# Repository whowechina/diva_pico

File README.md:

# Diva Pico - Project Diva Style Mini Controller
[点这里可以切换到中文版](README_CN.md)

Features:
* Two sizes, Diva Pico and Diva Pico+.
* It's small, but the buttons are still decent.
* Support Nintendo Switch, Steam PC and Arcade version.
* HID light for Arcade version.
* All source files open.

Thanks to many respectful guys/companies who made their tools or materials free or open source (KiCad, OnShape, InkScape, Raspberry things).

Special thanks to community developers that inspired me and helped me: CrazyRedMachine (https://github.com/CrazyRedMachine).

And also:
* GP2040-CE: https://gp2040-ce.info/ (for the PS4 support)
* RP_Silicon_KiCad: https://github.com/HeadBoffin/RP_Silicon_KiCad
* Switch_Keyboard_Kailh: https://github.com/kiswitch/keyswitch-kicad-library

## Notes
This Diva Pico project:  
* Heavily depends on 3D printing, you need a Bambu 3D printer (X1, P1 or A1, not the mini version).
* Requires skills to solder tiny components.

## My Other Projects
You can check out my other cool projects.

* Popn Pico: https://github.com/whowechina/popn_pico
* IIDX Pico: https://github.com/whowechina/iidx_pico
* Chu Pico: https://github.com/whowechina/chu_pico
* Mai Pico: https://github.com/whowechina/mai_pico
* Diva Pico: https://github.com/whowechina/diva_pico
* AIC Pico: https://github.com/whowechina/aic_pico
* Groove Pico: https://github.com/whowechina/groove_pico
* Geki Pico: https://github.com/whowechina/geki_pico
* Musec Pico: https://github.com/whowechina/musec_pico
* Ju Pico: https://github.com/whowechina/ju_pico
* Bishi Pico: https://github.com/whowechina/bishi_pico
* Nos Pico: https://github.com/whowechina/nos_pico
* Voltex Pico: https://github.com/whowechina/voltex_pico
* Chord Pico: https://github.com/whowechina/chord_pico
* Dance Pico: https://github.com/whowechina/dance_pico
* Arcade Pico: https://github.com/whowechina/arcade_pico

## **Disclaimer** ##
I made this project in my personal time with no financial benefit or sponsorship. I will continue to improve the project. I have done my best to ensure that everything is accurate and functional, there's always a chance that mistakes may occur. I cannot be held responsible for any loss of your time or money that may result from using this open source project. Thank you for your understanding.

## About the License
It's CC-NC. So DIY for yourself and for your friend, don't make money from it. And plagiarism that doesn’t even dare to mention the original author is not acceptable. Plase note that pooling orders and group buying for raw materials is acceptable. Selling off any leftover components without profit is also acceptable.

If you're interested in some kind of commercial use, please contact me (Discord, QQ group, Wechat group or leave your contact in issue section).

## My Discord Invitation
https://discord.gg/M8f2PPQFEA

## HOW TO BUILD
### Frequently Made Mistakes
Many DIY enthusiasts commonly make certain mistakes during the building process. Please proceed with extra caution to avoid these.
* **MISTAKE: Soldering everything together without conducting intermediate testing.**  
  Remember, even professional engineers can make mistakes. It becomes significantly harder to identify the root cause of a problem when all components are already assembled or soldered. Therefore, it's advisable to solder and test in stages. The firmware is designed to function correctly even with some components missing, which is good for testing.
* **MISTAKE: Neglecting to cut the ADDR pin trace on the MPR121 module.**  
  The MPR121 module in the market has the ADDR pin pre-connected to ground. But the board expects a floating ADDR pin, otherwise the ADDR pin will short the circuit. Please verify your "CUT" using a multimeter.
* **MISTAKE: Rushing to replace components when something fails.**  
  Sometimes people prematurely assumes that the Raspberry Pi Pico or other modules are faulty.
  Be aware that desoldering and soldering large SMD components is a challenging task. It carries the risk of damaging the component or the PCB board. Patience and caution are crucial. Look at the schematics and PCB design files and ask help from community first. Questioning the integrity of these components should be your last resort.

### PCB
* Choose a PCB vendor (such as JLCPCB) and place an order with the gerber zip file (latest `Production\PCB\diva_xxx_xxx.zip`), regular FR-4 board, black color, thickness is **1.6mm**.  

* 1x Rasberry Pico Pi Pico or **pin-to-pin** compatible clones.  
  https://www.raspberrypi.com/products/raspberry-pi-pico  
  Sticking a thin scotch tape to avoid short-circuit is a good idea.  

* 16x WS2812B-4020 (32x for Diva Pico+) side-facing RGB LEDs for the slider.  
  https://www.lcsc.com/product-detail/Light-Emitting-Diodes-LED_Worldsemi-WS2812B-4020_C965557.html
* 9x WS2812B-3528 RGB LEDs for Diva Pico buttons. For Diva Pico+, you need 17x WS2812B-3528 reverse mount RGB LEDs.

* 2x MPR121 modules (3x for Diva Pico+), there're many types in the market, choose ones like this.  
  https://www.sparkfun.com/products/retired/9695  
  Before solder MP121 module to the main PCB board, remember to use a knife to **cut (unshort) the tiny trace that connects ADDR to the GND**. You can cut the red part as shown in the image. Please be careful not to cut more than necessary.  

* 8x 0603 1uF (0.1~1uF all fine) capacitors (C1 to C8), OPTIONAL, recommended.

* 4x Kailh choc v1 switches, dark yellow is recommeded for its 70gf force.  

* 2x Alps SKSTAAE010 tactile switches.
  https://tech.alpsalpine.com/e/products/detail/SKSTAAE010/

* 1x Omron B3F-4005 or B3F-4000 micro-switch.
  https://www.mouser.com/ProductDetail/Omron-Electronics/B3F-4000?qs=B3tblJ0Nlt8c5sbFRctxww%3D%3D

* For Diva Pico only, 3M 5423 or 5421 UHMW PE film tape, important for button feel. 5423 is better for its thickness.  
  https://www.3m.com/3M/en_US/p/d/b40069119/

  You need to apply tapes to the contact surface of button to switch and button to base clamp.  

* For Diva Pico only, 4x 2mm\*50mm (diameter\*length) steel rods for the button lever structure.

* For Diva Pico+ only, 8x U-shape 2U stabilizer steel wires, you can also harvest them from regular 2U MX stabilizers. I invented this structure originally in my Voltex Pico project, checkout Voltex Pico repository for more details.

* For Diva Pico+ only, 4x 3mm\*5mm\*10mm regular springs for increasing the button force.

### Light Guide Panel
* Find a service to cut a light guide panel or a frosted acrylic panel. It's a perfect rectangle, 1.8mm to 2.0mm thickness
  * For Diva Pico, the size is 240mm\*42mm.
  * For Diva Pico+, the size is 329mm\*47mm.
* This is what a decent light guide panel looks like.  

### 3D Printing
* You might need a Bambu 3D printer:
  *  For Diva Pico, a 256\*256mm bed is fine; for Diva Pico+ you need a H2D-sized bed.
  * Its AMS system works great for multi-color printing.
* Printing parameters  
  * PLA, PETG, ABS are all OK.
  * The color "Arctic Whisper" works best for the main body.
  * Layer height: 0.2mm
  * Support: Yes, always.

* Base: `Production\3D\diva_xxx_base.stl`.
* Cover Base: `Production\3D\diva_xxx_support.stl`.
* Cover: `Production\3D\diva_xxx_panel.3mf`, with multi-color support.
* Buttons: `Production\3D\diva_xxx_button_combo.3mf`, with multi-color support.  
  Note that button components (the button body, the seat and the logos on it) are mixed in one file, you need to cherry-pick before printing.  

From top to bottom:
* Cover
* Cover Base + Light Guide Panel
* Buttons
* PCB
* Base

For Diva Pico, you need **6x M3*10mm regular screws** to fix all things. For Diva Pico+, you need **9x M3\*8mm** regular screws and **4x M2\*8mm** flat head screws.

Apply some 10mm\*2mm silicone anti-slip pads to the bottom side of the base to provide stability when playing.  

#### Button dome choices
* Go buy 60mm dome buttons.
  * For Diva Pico+, a regular 60mm arcade dome button is fine.
  * For Diva Pico, you should get this specific one, its inner diameter is 46mm.  

### Firmware
* UF2 file is in `Production\Firmware` folder.
* For the new build, hold the BOOTSEL button while connect the USB to a PC, there will be a disk named "RPI-RP2" showed up. Drag the UF2 firmware binary file into it. That's it. There's a small hole at the bottom side of the Diva Pico, it is facing right to the BOOTSEL button.
* It has a command line to do configuration. You can use this Web Serial Terminal to connect to the USB serial port of the Diva Pico. (Note: "?" is for help)  
  https://googlechromelabs.github.io/serial-terminal/  
* You can switch key mapping mode using either of the following methods:
  * Hold Triangle, Square, Cross, Circle or Cross+Circle while plugging in the USB cable to switch to Nintendo Switch, PC Steam, Arcade, PlayStation and PlayStation Arcade mode, respectively.
  * Use the `keymap` command in the command line interface.
* In Nintendo Switch, PC Steam, and PlayStation modes, the left auxiliary button is used as a "SHIFT" key, changing the functions of the other six buttons.
* In PlayStation mode, if key-related files are missing, the console will disconnect controller input after 8 minutes. You can use the following tool to set a PS key.  
  https://whowechina.github.io/diva_pico/tools/ps4key_packer.html
  * **Note** The Diva Pico project will not provide any files or information related to acquiring these files. Do not request them through any communication channel (e.g., Email, Instant Messaging, GitHub Issues, Discord).

## CAD Source File
I'm using OnShape free subscription. It's powerful but it can't archive original designs to local, so I can only share the link here. STL/DXF/DWG files are exported from this online document.  
https://cad.onshape.com/documents/d9e9c1de2d4b98d5eaf21d07/w/7c216f367b558e083eb1f468/e/4536bf9859137db81313ff87?configuration=List_ilV09d08Sdz7FZ%3DButton_48&renderMode=0&uiState=65923e1383b3106c15b5c996

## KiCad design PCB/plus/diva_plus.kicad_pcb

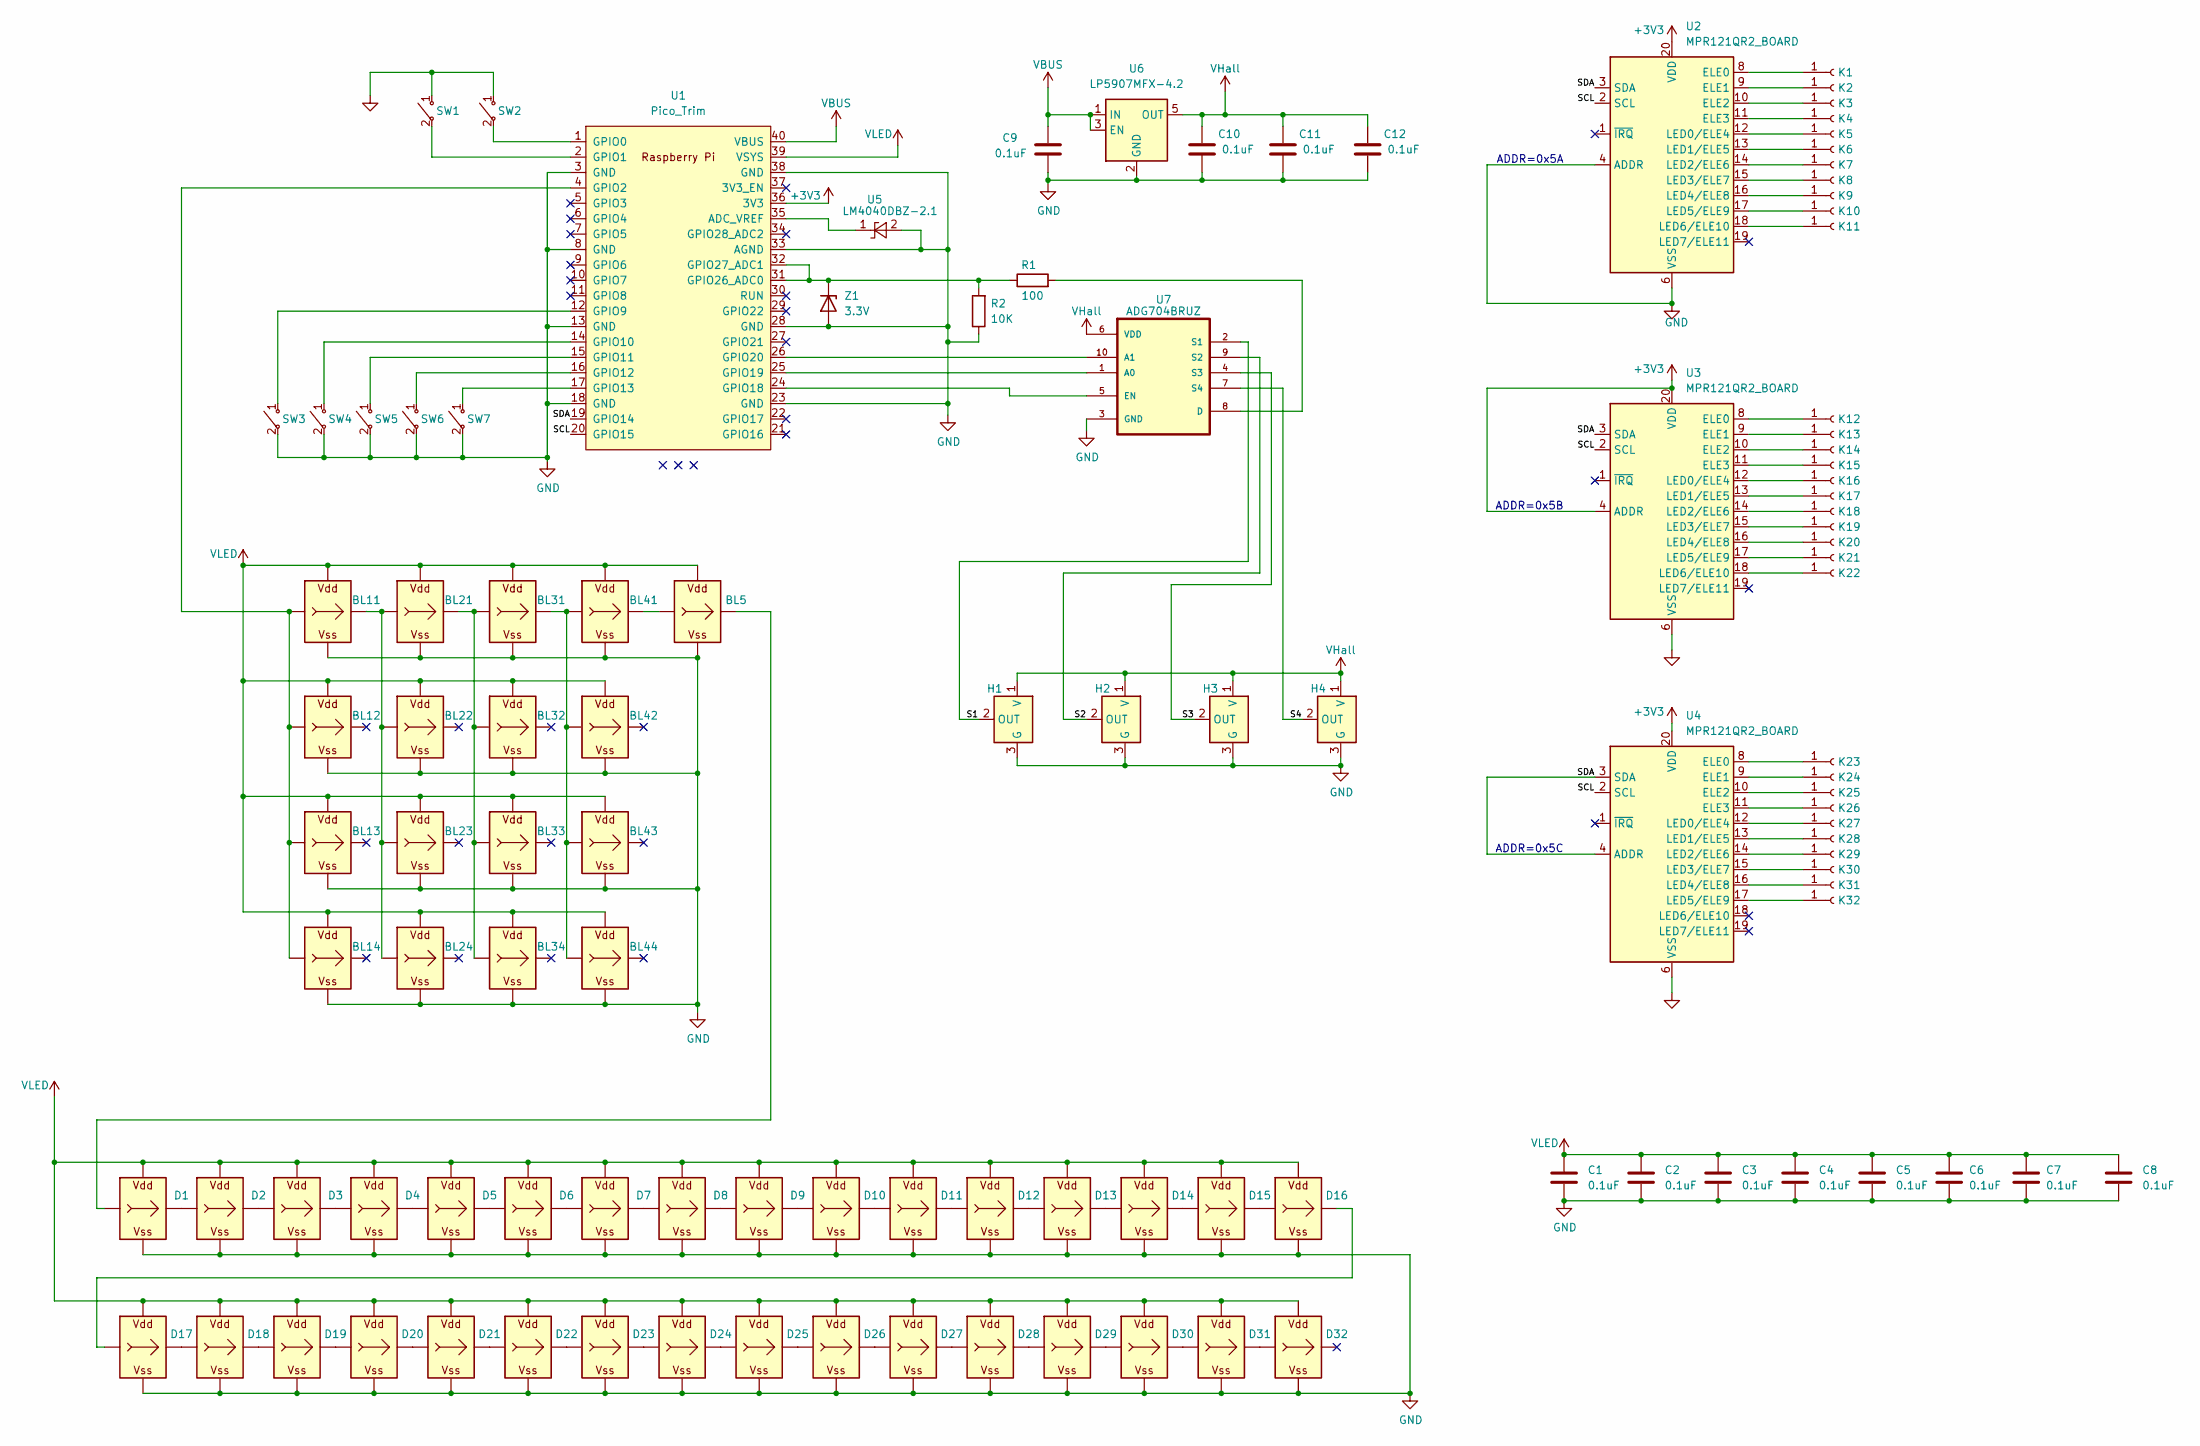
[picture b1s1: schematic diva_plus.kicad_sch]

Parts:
BL5, BL11, BL12, BL13, BL14, BL21, BL22, BL23, BL24, BL31, BL32, BL33, BL34, BL41, BL42, BL43, BL44: WS2812B_Unified; WS2812B-2835_EMBED
C1, C2, C3, C4, C5, C6, C7, C8, C9, C10, C11, C12: 0.1uF; C_0603_1608Metric_Pad1.08x0.95mm_HandSolder
D1, D2, D3, D4, D5, D6, D7, D8, D9, D10, D11, D12, D13, D14, D15, D16, D17, D18, D19, D20, D21, D22, D23, D24, D25, D26, D27, D28, D29, D30, D31, D32: WS2812B_Unified; WS2812B-4020
H1, H2, H3, H4: SS49E_SOT23; SOT-23-FAT
K1, K2, K3, K4, K5, K6, K7, K8, K9, K10, K13, K14, K15, K16, K18, K19, K20, K21, K24, K25, K26, K27, K28, K29, K30, K31, K32: Conn_01x01_Female; DivaKey
K11, K22: Conn_01x01_Female; DivaKeyBiasLeft
K12, K17, K23: Conn_01x01_Female; DivaKeyBiasRight
R1: 100; R_0603_1608Metric_Pad0.98x0.95mm_HandSolder
R2: 10K; R_0603_1608Metric_Pad0.98x0.95mm_HandSolder
SW1, SW2: SWITCH_SPST; SKSTAAE010
SW3, SW4, SW5, SW6: SWITCH_SPST; Choc_HE
SW7: SWITCH_SPST; B3F4000
U1: Pico_Trim; RPi_Pico_SMD_No_USB
U2, U3, U4: MPR121QR2_BOARD; MPR121_BOARD
U5: LM4040DBZ-2.1; SOT-23-FAT
U6: LP5907MFX-4.2; SOT-23-5
U7: ADG704BRUZ; TSSOP-10_3x3mm_P0.5mm
Z1: 3.3V; D_SOD-123F

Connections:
+3V3: U1.36 (3V3), U2.20 (VDD), U3.4 (ADDR), U3.20 (VDD), U4.20 (VDD)
/S1: H1.2 (OUT), U7.2 (S1)
/S2: H2.2 (OUT), U7.9 (S2)
/S3: H3.2 (OUT), U7.4 (S3)
/S4: H4.2 (OUT), U7.7 (S4)
/SCL: U1.20 (GPIO15), U2.2 (SCL), U3.2 (SCL), U4.2 (SCL)
/SDA: U1.19 (GPIO14), U2.3 (SDA), U3.3 (SDA), U4.3 (SDA), U4.4 (ADDR)
GND: BL5.G (VSS), BL11.G (VSS), BL12.G (VSS), BL13.G (VSS), BL14.G (VSS), BL21.G (VSS), BL22.G (VSS), BL23.G (VSS), BL24.G (VSS), BL31.G (VSS), BL32.G (VSS), BL33.G (VSS), BL34.G (VSS), BL41.G (VSS), BL42.G (VSS), BL43.G (VSS), BL44.G (VSS), C1.2, C2.2, C3.2, C4.2, C5.2, C6.2, C7.2, C8.2, C9.2, C10.2, C11.2, C12.2, D1.G (VSS), D2.G (VSS), D3.G (VSS), D4.G (VSS), D5.G (VSS), D6.G (VSS), D7.G (VSS), D8.G (VSS), D9.G (VSS), D10.G (VSS), D11.G (VSS), D12.G (VSS), D13.G (VSS), D14.G (VSS), D15.G (VSS), D16.G (VSS), D17.G (VSS), D18.G (VSS), D19.G (VSS), D20.G (VSS), D21.G (VSS), D22.G (VSS), D23.G (VSS), D24.G (VSS), D25.G (VSS), D26.G (VSS), D27.G (VSS), D28.G (VSS), D29.G (VSS), D30.G (VSS), D31.G (VSS), D32.G (VSS), H1.3 (G), H2.3 (G), H3.3 (G), H4.3 (G), R2.1, SW1.1 ("~"), SW2.1 ("~"), SW3.2 ("~"), SW4.2 ("~"), SW5.2 ("~"), SW6.2 ("~"), SW7.2 ("~"), U1.3 (GND), U1.8 (GND), U1.13 (GND), U1.18 (GND), U1.23 (GND), U1.28 (GND), U1.33 (AGND), U1.38 (GND), U2.4 (ADDR), U2.6 (VSS), U3.6 (VSS), U4.6 (VSS), U5.2 (A), U6.2 (GND), U7.3 (GND), Z1.2 (A)
unnamed: BL5.O (Out), D1.I (In)
unnamed: BL11.I (In), BL12.I (In), BL13.I (In), BL14.I (In), U1.4 (GPIO2)
unnamed: BL11.O (Out), BL21.I (In), BL22.I (In), BL23.I (In), BL24.I (In)
unnamed: BL21.O (Out), BL31.I (In), BL32.I (In), BL33.I (In), BL34.I (In)
unnamed: BL31.O (Out), BL41.I (In), BL42.I (In), BL43.I (In), BL44.I (In)
unnamed: BL5.I (In), BL41.O (Out)
unnamed: D1.O (Out), D2.I (In)
unnamed: D2.O (Out), D3.I (In)
unnamed: D3.O (Out), D4.I (In)
unnamed: D4.O (Out), D5.I (In)
unnamed: D5.O (Out), D6.I (In)
unnamed: D6.O (Out), D7.I (In)
unnamed: D7.O (Out), D8.I (In)
unnamed: D8.O (Out), D9.I (In)
unnamed: D9.O (Out), D10.I (In)
unnamed: D10.O (Out), D11.I (In)
unnamed: D11.O (Out), D12.I (In)
unnamed: D12.O (Out), D13.I (In)
unnamed: D13.O (Out), D14.I (In)
unnamed: D14.O (Out), D15.I (In)
unnamed: D15.O (Out), D16.I (In)
unnamed: D16.O (Out), D17.I (In)
unnamed: D17.O (Out), D18.I (In)
unnamed: D18.O (Out), D19.I (In)
unnamed: D19.O (Out), D20.I (In)
unnamed: D20.O (Out), D21.I (In)
unnamed: D21.O (Out), D22.I (In)
unnamed: D22.O (Out), D23.I (In)
unnamed: D23.O (Out), D24.I (In)
unnamed: D24.O (Out), D25.I (In)
unnamed: D25.O (Out), D26.I (In)
unnamed: D26.O (Out), D27.I (In)
unnamed: D27.O (Out), D28.I (In)
unnamed: D28.O (Out), D29.I (In)
unnamed: D29.O (Out), D30.I (In)
unnamed: D30.O (Out), D31.I (In)
unnamed: D31.O (Out), D32.I (In)
unnamed: K1.1, U2.8 (ELE0)
unnamed: K2.1, U2.9 (ELE1)
unnamed: K3.1, U2.10 (ELE2)
unnamed: K4.1, U2.11 (ELE3)
unnamed: K5.1, U2.12 (LED0/ELE4)
unnamed: K6.1, U2.13 (LED1/ELE5)
unnamed: K7.1, U2.14 (LED2/ELE6)
unnamed: K8.1, U2.15 (LED3/ELE7)
unnamed: K9.1, U2.16 (LED4/ELE8)
unnamed: K10.1, U2.17 (LED5/ELE9)
unnamed: K11.1, U2.18 (LED6/ELE10)
unnamed: K12.1, U3.8 (ELE0)
unnamed: K13.1, U3.9 (ELE1)
unnamed: K14.1, U3.10 (ELE2)
unnamed: K15.1, U3.11 (ELE3)
unnamed: K16.1, U3.12 (LED0/ELE4)
unnamed: K17.1, U3.13 (LED1/ELE5)
unnamed: K18.1, U3.14 (LED2/ELE6)
unnamed: K19.1, U3.15 (LED3/ELE7)
unnamed: K20.1, U3.16 (LED4/ELE8)
unnamed: K21.1, U3.17 (LED5/ELE9)
unnamed: K22.1, U3.18 (LED6/ELE10)
unnamed: K23.1, U4.8 (ELE0)
unnamed: K24.1, U4.9 (ELE1)
unnamed: K25.1, U4.10 (ELE2)
unnamed: K26.1, U4.11 (ELE3)
unnamed: K27.1, U4.12 (LED0/ELE4)
unnamed: K28.1, U4.13 (LED1/ELE5)
unnamed: K29.1, U4.14 (LED2/ELE6)
unnamed: K30.1, U4.15 (LED3/ELE7)
unnamed: K31.1, U4.16 (LED4/ELE8)
unnamed: K32.1, U4.17 (LED5/ELE9)
unnamed: U1.35 (ADC_VREF), U5.1 (K)
unnamed: SW2.2 ("~"), U1.1 (GPIO0)
unnamed: SW1.2 ("~"), U1.2 (GPIO1)
unnamed: SW3.1 ("~"), U1.12 (GPIO9)
unnamed: SW4.1 ("~"), U1.14 (GPIO10)
unnamed: SW5.1 ("~"), U1.15 (GPIO11)
unnamed: SW6.1 ("~"), U1.16 (GPIO12)
unnamed: SW7.1 ("~"), U1.17 (GPIO13)
unnamed: U1.24 (GPIO18), U7.5 (EN)
unnamed: U1.25 (GPIO19), U7.1 (A0)
unnamed: U1.26 (GPIO20), U7.10 (A1)
unnamed: R1.1, R2.2, U1.31 (GPIO26_ADC0), U1.32 (GPIO27_ADC1), Z1.1 (K)
unnamed: R1.2, U7.8 (D)
VBUS: C9.1, U1.40 (VBUS), U6.1 (IN), U6.3 (EN)
VHall: C10.1, C11.1, C12.1, H1.1 (V), H2.1 (V), H3.1 (V), H4.1 (V), U6.5 (OUT), U7.6 (VDD)
VLED: BL5.V (VDD), BL11.V (VDD), BL12.V (VDD), BL13.V (VDD), BL14.V (VDD), BL21.V (VDD), BL22.V (VDD), BL23.V (VDD), BL24.V (VDD), BL31.V (VDD), BL32.V (VDD), BL33.V (VDD), BL34.V (VDD), BL41.V (VDD), BL42.V (VDD), BL43.V (VDD), BL44.V (VDD), C1.1, C2.1, C3.1, C4.1, C5.1, C6.1, C7.1, C8.1, D1.V (VDD), D2.V (VDD), D3.V (VDD), D4.V (VDD), D5.V (VDD), D6.V (VDD), D7.V (VDD), D8.V (VDD), D9.V (VDD), D10.V (VDD), D11.V (VDD), D12.V (VDD), D13.V (VDD), D14.V (VDD), D15.V (VDD), D16.V (VDD), D17.V (VDD), D18.V (VDD), D19.V (VDD), D20.V (VDD), D21.V (VDD), D22.V (VDD), D23.V (VDD), D24.V (VDD), D25.V (VDD), D26.V (VDD), D27.V (VDD), D28.V (VDD), D29.V (VDD), D30.V (VDD), D31.V (VDD), D32.V (VDD), U1.39 (VSYS)

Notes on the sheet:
ADDR=0x5C
ADDR=0x5A
ADDR=0x5B

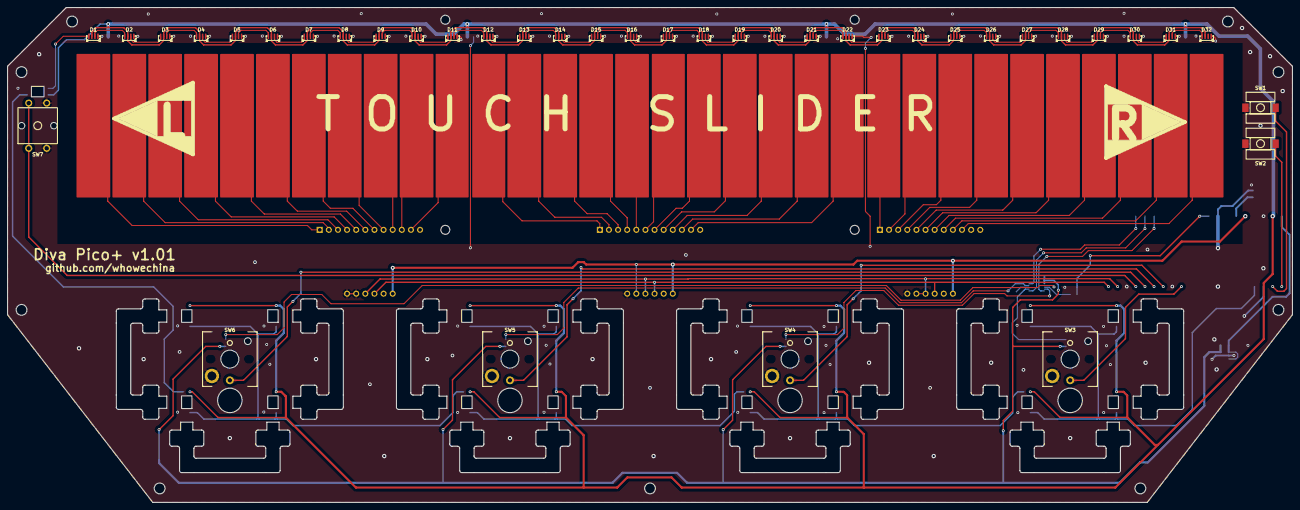
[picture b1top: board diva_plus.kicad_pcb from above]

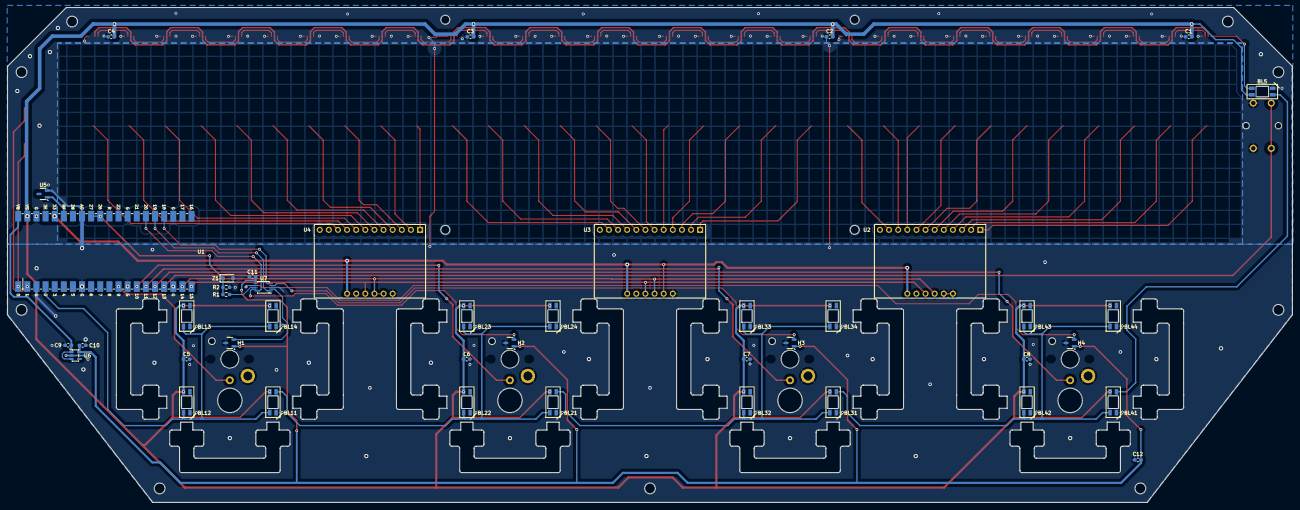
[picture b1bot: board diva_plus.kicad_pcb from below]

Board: 2 copper layers, 357.8 x 137.8 mm, 114 parts (43 on the bottom side), 93 nets.

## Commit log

2023-12-16 PCB work just started
2023-12-17 PCB layout done
2023-12-17 PCB v1.0 ready
2023-12-24 Firmware work begins
2023-12-31 Works on PC version
2023-12-31 Nintendo Switch works too
2024-01-01 To publish
2024-01-01 Minor markdown format issue fixed
2024-03-03 README in Chinese
2024-07-06 Firmware cleanups
2024-07-15 Cross-reference to new Groove Pico
2024-09-05 Thanks to some projects
2024-10-18 Cross-reference and Discord invitation
2025-02-12 Fix file names
2025-02-14 Fix getchar return handling
2025-02-14 Add include clocks.h for newer SDK
2025-02-14 Welcome in CLI
2025-02-14 Flowing rainbow lights
2025-02-14 Better HID reporting
2025-02-14 Improved housing
2025-02-14 PCB v1.1 (minor optimization)
2025-02-14 More screws in housing
2025-02-28 Fix filter and sense command
2025-03-02 Picture of a decent LGP
2025-03-02 Cross-ref to Ju Pico
2025-03-12 Update base for Pico clearance
2025-03-22 Remove USB pin soldering warning
2025-03-22 Update PCB vendor lines in guide
2025-03-22 Update base to reduce bend
2025-03-27 Remove unnessary options, focus on best one
2025-04-04 Cross-reference to new projects
2025-04-19 Debouncing freeze time to 15ms
2025-04-21 Fix diva base USB hole position
2025-05-02 Stronger button platform
2025-08-24 Periodic HID report to pass selftest
2025-08-25 Keymap setting for Switch|Steam|Arcade
2025-08-25 Update readme for keymap presets
2025-08-26 Fix and clean-up lights
2025-08-26 Fix HID axis error introduced earlier
2025-08-26 Better button light color
2025-08-26 Stronger panel screw holes
2025-10-14 Finetune button seat
2025-12-07 Rename old PCB as pico
2025-12-07 Start PCB work of diva plus
2025-12-12 Firmware support for Diva Pico+
2025-12-12 Auto update building time
2025-12-13 Separate slider and button level
2025-12-13 Remove nkro
2025-12-15 Arcade light support
2025-12-15 Arcade lights on both diva and diva+
2026-01-07 Diva Pico+ files
2026-01-09 Fix RGB order issue
2026-01-09 Fix cb re-entry buffer overwrite
2026-01-30 Finetune square sign
2026-02-11 Minor footprint and silkscreen finetune
2026-03-03 Better base thread holes
2026-03-03 Including diva+ in Readme
2026-03-11 Doc reference update
2026-04-06 Diva button finetune (lower limiter/ears)
2026-04-08 Fix header inclusion
2026-04-12 Add partial PS4 support (no auth)
2026-04-12 Better logic identifying Diva and Diva+
2026-04-12 Improve savedata module
2026-04-12 Put serial number in HID
2026-04-12 Slider debug feature
2026-04-12 Slider to joystick kinda works
2026-04-12 Thanks to GP2040-CE
2026-04-12 PS4 support, but no auth
2026-04-12 Key pack and upload mechanism
2026-04-13 Redboard file for PD loader
2026-04-13 PS4key import
2026-04-13 Side buttons mapped to HAT up/down in PS4 mode
2026-04-13 Parse RSA key at the packer side
2026-04-14 Log feature in savedata
2026-04-14 PS4 authentication (not working yet)
2026-04-15 Remove pwm lib
2026-04-15 Fix serial encoding in auth
2026-04-16 Clean-up ps auth code
2026-04-17 Direct save from packer
2026-04-17 Minor style change
2026-04-17 UF2 with PS4 support
2026-04-17 Fix slider breath effect
2026-04-22 Better HID keymap
2026-04-22 Better PS4 slider action
2026-04-22 Key related update in readme
2026-04-22 A little higher sensitivity by default
2026-04-23 Fix Steam mode keymap
2026-05-22 Fix PS mode not working issue (introduced earlier)
2026-06-04 Diva pico button base finetune
2026-06-04 Support Plyastation arcade mode
2026-06-13 Fix LED logic
2026-06-24 Update guide for Diva Pico+
